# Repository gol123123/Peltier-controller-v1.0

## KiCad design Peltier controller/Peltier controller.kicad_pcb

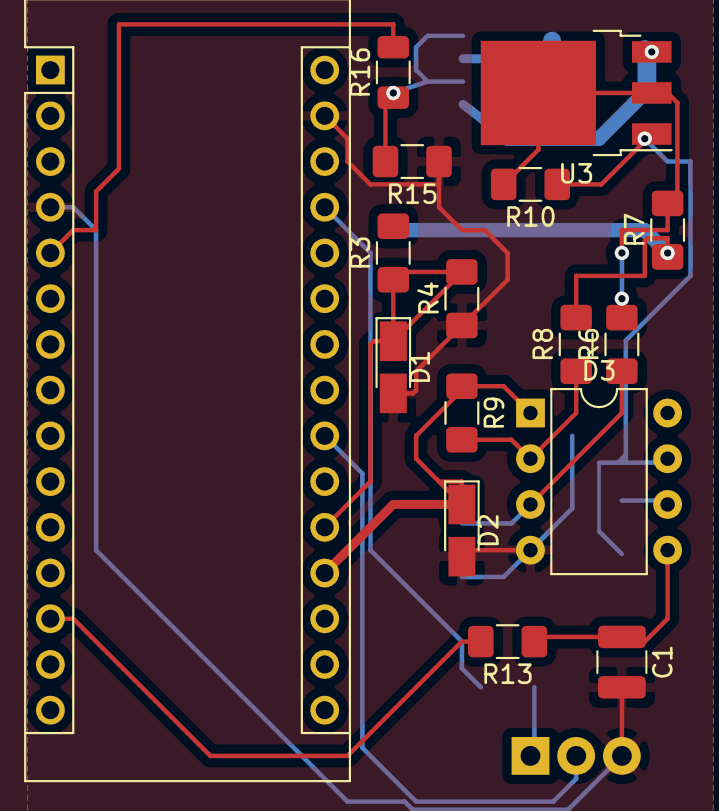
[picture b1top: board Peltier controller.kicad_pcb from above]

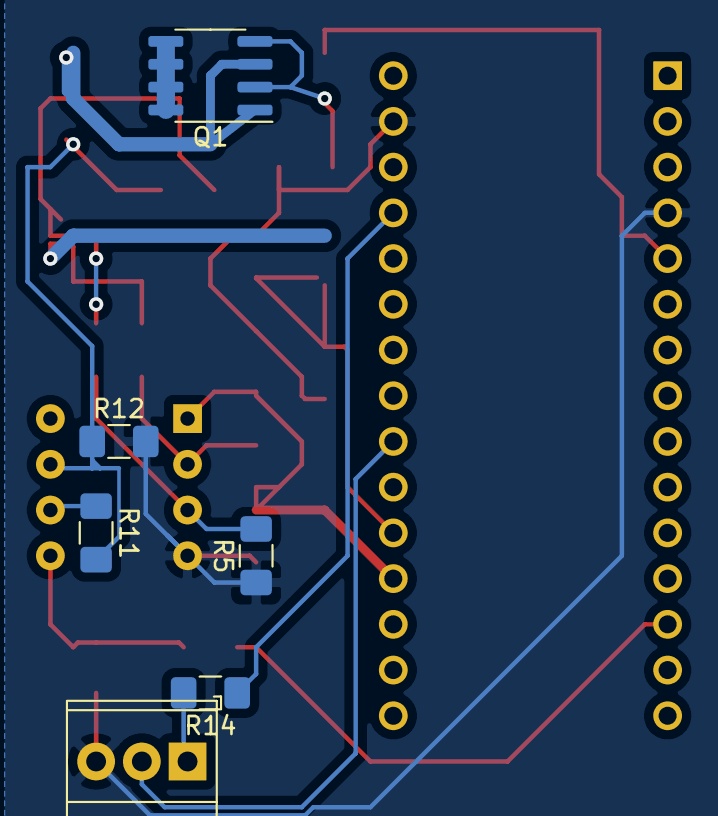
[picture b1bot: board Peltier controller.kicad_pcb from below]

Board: 2 copper layers, 22 parts (6 on the bottom side), 17 nets.

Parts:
A1: Arduino_Nano_v3.x; Arduino_Nano
C1: 10u; C_1210_3225Metric
D1, D2: 1N53xxB; D_MicroMELF_Handsoldering
D3: lm358_11; DIP-8_W7.62mm
Q1: IRF7324; SOIC-8_3.9x4.9mm_P1.27mm
R3, R4: 100K; C_1206_3216Metric_Pad1.42x1.75mm_HandSolder
R5, R9: 200K; C_1206_3216Metric_Pad1.42x1.75mm_HandSolder
R6, R11: 100k; C_1206_3216Metric_Pad1.42x1.75mm_HandSolder
R7: 0.1; C_1206_3216Metric_Pad1.42x1.75mm_HandSolder
R8: 10k; C_1206_3216Metric_Pad1.42x1.75mm_HandSolder
R10: 330; C_1206_3216Metric_Pad1.42x1.75mm_HandSolder
R12: 80k; C_1206_3216Metric_Pad1.42x1.75mm_HandSolder
R13: 200k; C_1206_3216Metric_Pad1.42x1.75mm_HandSolder
R14: 4k; C_1206_3216Metric_Pad1.42x1.75mm_HandSolder
R15: 20k; C_1206_3216Metric_Pad1.42x1.75mm_HandSolder
R16: 100; C_1206_3216Metric
U3: LM317_TO-252; TO-252-3_TabPin2
U10: LM355; TerminalBlock_TE_282834-3_1x03_P2.54mm_Horizontal

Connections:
/1: A1.19, D2.1, D3.1, R9.1
/A1: A1.20, D1.1, R3.1, R4.2
GND: A1.4, A1.29, C1.2, D1.2, D2.2, D3.4, R4.1, R5.1, R12.2, R15.1, U10.3
unnamed: A1.5, R16.2
unnamed: A1.13, R13.2
unnamed: A1.22, U10.2
unnamed: A1.27, R14.1
unnamed: C1.1, D3.5, R13.1
unnamed: D3.2, R8.1, R9.2
unnamed: D3.3, R5.2, R6.1
unnamed: D3.6, R11.1
unnamed: D3.7, R10.1, R11.2, R12.1, U3.1
unnamed: Q1.2, R15.2, R16.1
unnamed: Q1.7, Q1.8
unnamed: R3.2, R7.1, R8.2
unnamed: R6.2, R7.2, R10.2, U3.2
unnamed: R14.2, U10.1

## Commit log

2020-08-31 v1.0
2020-08-31 v2.0
2020-09-05 three commit
